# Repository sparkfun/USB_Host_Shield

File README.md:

SparkFun USB Host Shield
========================

[*SparkFun USB Host Shield (DEV-09947)*](https://www.sparkfun.com/products/9947)

The SparkFun USB Host Shield contains all of the digital logic and analog circuitry necessary to implement a full-speed USB peripheral/host controller with your Arduino. 

Repository Contents
-------------------
* **/Hardware** - All Eagle design files (.brd, .sch)

License Information
-------------------
The hardware is released under [Creative Commons ShareAlike 4.0 International](https://creativecommons.org/licenses/by-sa/4.0/).

Distributed as-is; no warranty is given.

_Check out the original USB Host Shield site from Circuits@Home [here](https://chome.nerpa.tech/arduino_usb_host_shield_projects/)._

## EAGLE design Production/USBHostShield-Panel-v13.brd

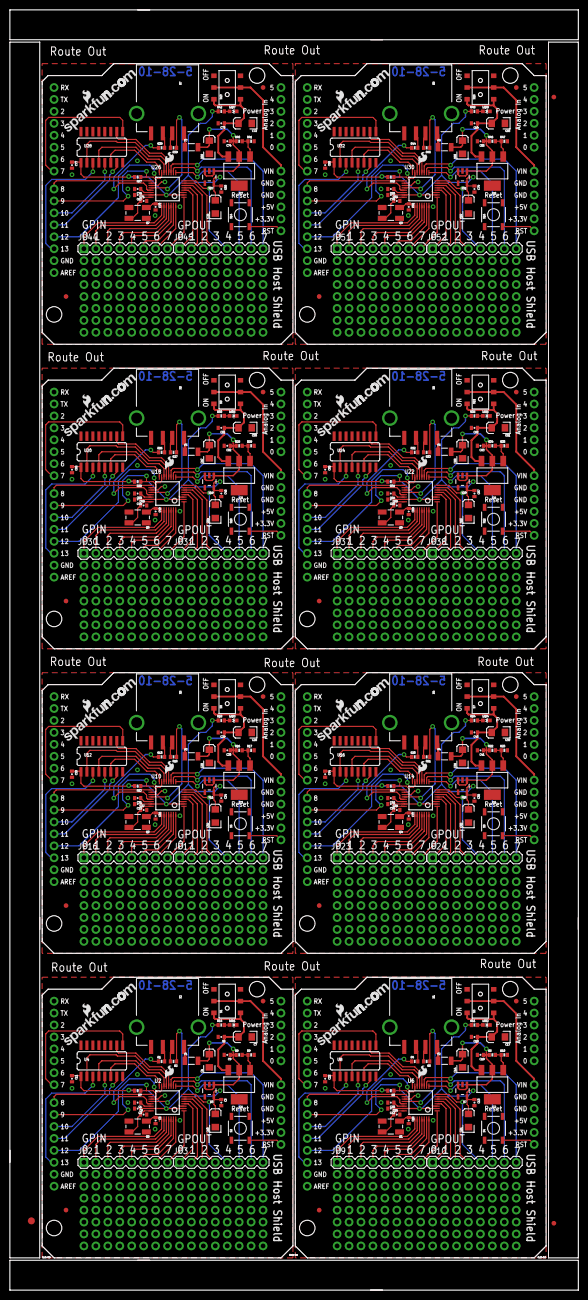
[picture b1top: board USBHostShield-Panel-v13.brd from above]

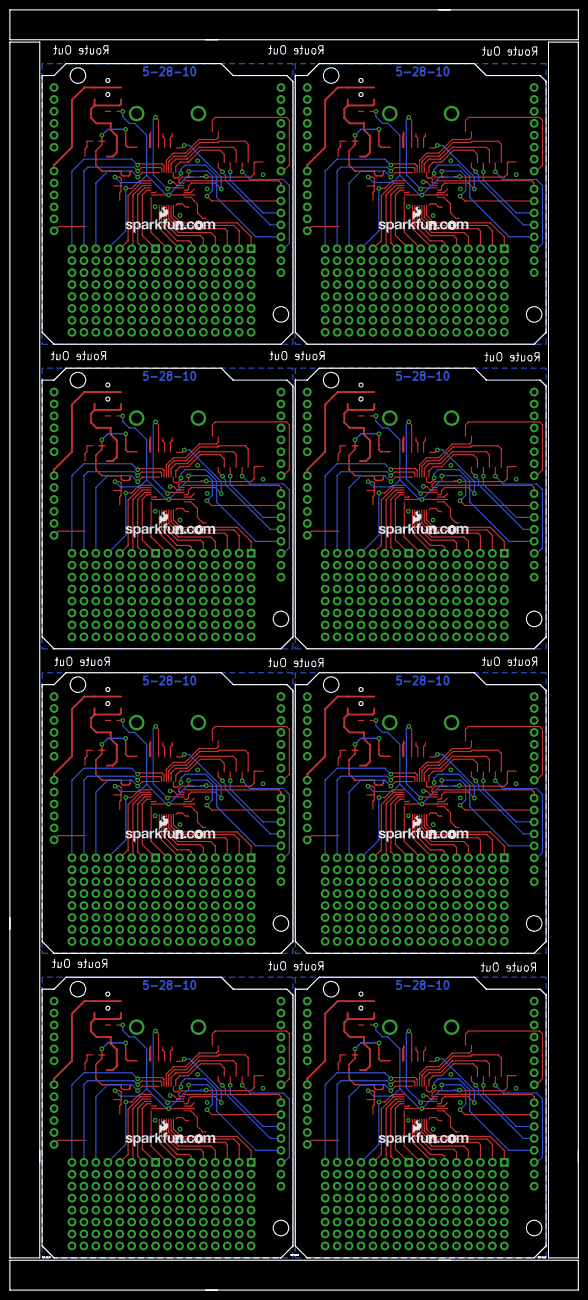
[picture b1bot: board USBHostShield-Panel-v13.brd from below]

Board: 2 copper layers, 120.9 x 272.2 mm, 283 parts (8 on the bottom side), 344 nets.

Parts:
C1, C2, C3, C8, C9, C11, C12, C13, C18, C19, C20, C22, C23, C24, C29, C30, C31, C33, C34, C35, C40, C41, C42, C44, C45, C46, C51, C52, C53, C55, C56, C57, C62, C63, C64, C66, C67, C68, C73, C74, C75, C77, C78, C79, C84, C85, C86, C88: 0.1uF; 0402-CAP
C4, C7, C10, C14, C17, C21, C25, C28, C32, C36, C39, C43, C47, C50, C54, C58, C61, C65, C69, C72, C76, C80, C83, C87: 10uF; EIA3216
C5, C6, C15, C16, C26, C27, C37, C38, C48, C49, C59, C60, C70, C71, C81, C82: 18pF; 0402-CAP
E$1: FIDUCIAL-1.5X3
E$2, E$5: FIDUCIAL-1X2
F1, F2, F3, F4, F5, F6, F7, F8: PTCSMD; PTC-1206
IC1, IC2, IC3, IC4, IC5, IC6, IC7, IC8: lm1117; SOT223
JP1, JP5, JP8, JP11, JP15, JP18, JP22, JP25, JP29, JP32, JP36, JP39, JP43, JP46, JP50, JP53: LOGO-SFENEW; SFE-NEW-WEBLOGO
JP2, JP9, JP16, JP23, JP30, JP37, JP44, JP51: GPIN; 1X08
JP3, JP10, JP17, JP24, JP31, JP38, JP45, JP52: GPOUT; 1X08
JP4, JP12, JP19, JP26, JP33, JP40, JP47, JP54: LOGO-SFESK; SFE-LOGO-FLAME
JP6, JP7, JP13, JP14, JP20, JP21, JP27, JP28, JP34, JP35, JP41, JP42, JP48, JP49, JP55, JP56: FIDUCIAL1X2; FIDUCIAL-1X2
LED1, LED2, LED3, LED4, LED5, LED6, LED7, LED8: red; LED-0603
Q1, Q2, Q3, Q4, Q5, Q6, Q7, Q8: 12MHz; CRYSTAL-SMD-5X3
R1, R2, R4, R5, R13, R15, R20, R21, R26, R27, R32, R33, R38, R39, R44, R45: 33; 0402-RES
R3, R7, R12, R19, R25, R31, R37, R43: 2.2K; 0402-RES
R6, R8, R16, R22, R28, R34, R40, R46: 240; 0402-RES
R9, R10, R17, R23, R29, R35, R41, R47: 715; 0402-RES
R11, R14, R18, R24, R30, R36, R42, R48: 330; 0402-RES
S1, S3, S5, S7, S9, S11, S13, S15: SWITCH-DPDTSMD; AYZ0202
S2, S4, S6, S8, S10, S12, S14, S16: SWITCH-SMD; TACTILE_SWITCH_SMD
U1, U5, U9, U13, U17, U21, U25, U29: ARDUINO_SHIELD; DUEMILANOVE_SHIELD
U2, U6, U10, U14, U18, U22, U26, U30: MAX3421E; TQFP32-5MM
U3, U7, U11, U15, U19, U23, U27, U31: 3.3V_REG; SOT23-5
U4, U8, U12, U16, U20, U24, U28, U32: HEX_CONVERTER; SO016
X1, X2, X3, X4, X5, X6, X7, X8: USB_; USB-A-S-SILK-FEMALE

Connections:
3.3V: C2.1, C3.1, C10.A, C11.1, R7.2, R14.1, U2.2, U2.23, U3.5, U4.1
3.3V1: C12.1, C13.1, C21.A, C22.1, R3.2, R11.1, U6.2, U6.23, U7.5, U8.1
3.3V2: C23.1, C24.1, C32.A, C33.1, R12.2, R18.1, U10.2, U10.23, U11.5, U12.1
3.3V3: C34.1, C35.1, C43.A, C44.1, R19.2, R24.1, U14.2, U14.23, U15.5, U16.1
3.3V4: C45.1, C46.1, C54.A, C55.1, R25.2, R30.1, U18.2, U18.23, U19.5, U20.1
3.3V5: C56.1, C57.1, C65.A, C66.1, R31.2, R36.1, U22.2, U22.23, U23.5, U24.1
3.3V6: C67.1, C68.1, C76.A, C77.1, R37.2, R42.1, U26.2, U26.23, U27.5, U28.1
3.3V7: C78.1, C79.1, C87.A, C88.1, R43.2, R48.1, U30.2, U30.23, U31.5, U32.1
5V: C4.A, C9.1, F1.2, IC1.2, R8.1, U3.1, U3.3
5V1: C14.A, C19.1, F2.2, IC2.2, R6.1, U7.1, U7.3
5V2: C25.A, C30.1, F3.2, IC3.2, R16.1, U11.1, U11.3
5V3: C36.A, C41.1, F4.2, IC4.2, R22.1, U15.1, U15.3
5V4: C47.A, C52.1, F5.2, IC5.2, R28.1, U19.1, U19.3
5V5: C58.A, C63.1, F6.2, IC6.2, R34.1, U23.1, U23.3
5V6: C69.A, C74.1, F7.2, IC7.2, R40.1, U27.1, U27.3
5V7: C80.A, C85.1, F8.2, IC8.2, R46.1, U31.1, U31.3
GND: C1.2, C2.2, C3.2, C4.C, C5.2, C6.2, C7.C, C8.2, C9.2, C10.C, C11.2, LED1.C, R9.2, S2.1, U1.GND@0, U1.GND@1, U1.GND@2, U2.3, U2.19, U3.2, U4.8, X2.GND
GND1: C12.2, C13.2, C14.C, C15.2, C16.2, C17.C, C18.2, C19.2, C20.2, C21.C, C22.2, LED2.C, R10.2, S4.1, U5.GND@0, U5.GND@1, U5.GND@2, U6.3, U6.19, U7.2, U8.8, X1.GND
GND2: C23.2, C24.2, C25.C, C26.2, C27.2, C28.C, C29.2, C30.2, C31.2, C32.C, C33.2, LED3.C, R17.2, S6.1, U9.GND@0, U9.GND@1, U9.GND@2, U10.3, U10.19, U11.2, U12.8, X3.GND
GND3: C34.2, C35.2, C36.C, C37.2, C38.2, C39.C, C40.2, C41.2, C42.2, C43.C, C44.2, LED4.C, R23.2, S8.1, U13.GND@0, U13.GND@1, U13.GND@2, U14.3, U14.19, U15.2, U16.8, X4.GND
GND4: C45.2, C46.2, C47.C, C48.2, C49.2, C50.C, C51.2, C52.2, C53.2, C54.C, C55.2, LED5.C, R29.2, S10.1, U17.GND@0, U17.GND@1, U17.GND@2, U18.3, U18.19, U19.2, U20.8, X5.GND
GND5: C56.2, C57.2, C58.C, C59.2, C60.2, C61.C, C62.2, C63.2, C64.2, C65.C, C66.2, LED6.C, R35.2, S12.1, U21.GND@0, U21.GND@1, U21.GND@2, U22.3, U22.19, U23.2, U24.8, X6.GND
GND6: C67.2, C68.2, C69.C, C70.2, C71.2, C72.C, C73.2, C74.2, C75.2, C76.C, C77.2, LED7.C, R41.2, S14.1, U25.GND@0, U25.GND@1, U25.GND@2, U26.3, U26.19, U27.2, U28.8, X7.GND
GND7: C78.2, C79.2, C80.C, C81.2, C82.2, C83.C, C84.2, C85.2, C86.2, C87.C, C88.2, LED8.C, R47.2, S16.1, U29.GND@0, U29.GND@1, U29.GND@2, U30.3, U30.19, U31.2, U32.8, X8.GND
GPX: U1.D8, U2.17
GPX1: U5.D8, U6.17
GPX2: U9.D8, U10.17
GPX3: U13.D8, U14.17
GPX4: U17.D8, U18.17
GPX5: U21.D8, U22.17
GPX6: U25.D8, U26.17
GPX7: U29.D8, U30.17
INT: R7.1, U1.D9, U2.18
INT1: R3.1, U5.D9, U6.18
INT2: R12.1, U9.D9, U10.18
INT3: R19.1, U13.D9, U14.18
INT4: R25.1, U17.D9, U18.18
INT5: R31.1, U21.D9, U22.18
INT6: R37.1, U25.D9, U26.18
INT7: R43.1, U29.D9, U30.18
MISO: U1.D12, U2.15
MISO1: U5.D12, U6.15
MISO2: U9.D12, U10.15
MISO3: U13.D12, U14.15
MISO4: U17.D12, U18.15
MISO5: U21.D12, U22.15
MISO6: U25.D12, U26.15
MISO7: U29.D12, U30.15
MOSI: U1.D11, U4.7
MOSI1: U5.D11, U8.7
MOSI2: U9.D11, U12.7
MOSI3: U13.D11, U16.7
MOSI4: U17.D11, U20.7
MOSI5: U21.D11, U24.7
MOSI6: U25.D11, U28.7
MOSI7: U29.D11, U32.7
MOSI-IN: U2.16, U4.6
MOSI-IN1: U6.16, U8.6
MOSI-IN2: U10.16, U12.6
MOSI-IN3: U14.16, U16.6
MOSI-IN4: U18.16, U20.6
MOSI-IN5: U22.16, U24.6
MOSI-IN6: U26.16, U28.6
MOSI-IN7: U30.16, U32.6
unnamed: JP2.8, U2.1
unnamed: R2.1, U2.20
unnamed: R1.1, U2.21
unnamed: JP3.1, U2.4
unnamed: R1.2, X2.D+
unnamed: JP3.2, U2.5
unnamed: JP3.3, U2.6
unnamed: R2.2, X2.D-
unnamed: C5.1, Q2.1, U2.25
unnamed: C6.1, Q2.3, U2.24
unnamed: IC1.1, R8.2, R9.1
unnamed: S2.3, U1.RES
unnamed: JP3.4, U2.7
unnamed: JP3.5, U2.8
unnamed: JP3.6, U2.9
unnamed: JP3.7, U2.10
unnamed: JP3.8, U2.11
unnamed: JP2.7, U2.32
unnamed: JP2.6, U2.31
unnamed: JP2.5, U2.30
unnamed: JP2.4, U2.29
unnamed: JP2.3, U2.28
unnamed: JP2.2, U2.27
unnamed: JP2.1, U2.26
unnamed: LED1.A, R14.2
unnamed: F1.1, X2.VBUS
unnamed: R4.2, X1.D+
unnamed: R5.2, X1.D-
unnamed: R5.1, U6.20
unnamed: R4.1, U6.21
unnamed: C15.1, Q1.1, U6.25
unnamed: C16.1, Q1.3, U6.24
unnamed: IC2.1, R6.2, R10.1
unnamed: JP9.8, U6.1
unnamed: JP10.1, U6.4
unnamed: JP10.2, U6.5
unnamed: JP10.3, U6.6
unnamed: JP10.4, U6.7
unnamed: JP10.5, U6.8
unnamed: JP10.6, U6.9
unnamed: JP10.7, U6.10
unnamed: JP10.8, U6.11
unnamed: JP9.7, U6.32
unnamed: JP9.6, U6.31
unnamed: JP9.5, U6.30
unnamed: JP9.4, U6.29
unnamed: JP9.3, U6.28
unnamed: JP9.2, U6.27
unnamed: JP9.1, U6.26
unnamed: S4.3, U5.RES
unnamed: LED2.A, R11.2
unnamed: F2.1, X1.VBUS
unnamed: R13.2, X3.D+
unnamed: R15.2, X3.D-
unnamed: R15.1, U10.20
unnamed: R13.1, U10.21
unnamed: C26.1, Q3.1, U10.25
unnamed: C27.1, Q3.3, U10.24
unnamed: IC3.1, R16.2, R17.1
unnamed: JP16.8, U10.1
unnamed: JP17.1, U10.4
unnamed: JP17.2, U10.5
unnamed: JP17.3, U10.6
unnamed: JP17.4, U10.7
unnamed: JP17.5, U10.8
unnamed: JP17.6, U10.9
unnamed: JP17.7, U10.10
unnamed: JP17.8, U10.11
unnamed: JP16.7, U10.32
unnamed: JP16.6, U10.31
unnamed: JP16.5, U10.30
unnamed: JP16.4, U10.29
unnamed: JP16.3, U10.28
unnamed: JP16.2, U10.27
unnamed: JP16.1, U10.26
unnamed: S6.3, U9.RES
unnamed: LED3.A, R18.2
unnamed: F3.1, X3.VBUS
unnamed: R20.2, X4.D+
unnamed: R21.2, X4.D-
unnamed: R21.1, U14.20
unnamed: R20.1, U14.21
unnamed: C37.1, Q4.1, U14.25
unnamed: C38.1, Q4.3, U14.24
unnamed: IC4.1, R22.2, R23.1
unnamed: JP23.8, U14.1
unnamed: JP24.1, U14.4
unnamed: JP24.2, U14.5
unnamed: JP24.3, U14.6
unnamed: JP24.4, U14.7
unnamed: JP24.5, U14.8
unnamed: JP24.6, U14.9
unnamed: JP24.7, U14.10
unnamed: JP24.8, U14.11
unnamed: JP23.7, U14.32
unnamed: JP23.6, U14.31
unnamed: JP23.5, U14.30
unnamed: JP23.4, U14.29
unnamed: JP23.3, U14.28
unnamed: JP23.2, U14.27
unnamed: JP23.1, U14.26
unnamed: S8.3, U13.RES
unnamed: LED4.A, R24.2
unnamed: F4.1, X4.VBUS
unnamed: R26.2, X5.D+
unnamed: R27.2, X5.D-
unnamed: R27.1, U18.20
unnamed: R26.1, U18.21
unnamed: C48.1, Q5.1, U18.25
unnamed: C49.1, Q5.3, U18.24
unnamed: IC5.1, R28.2, R29.1
unnamed: JP30.8, U18.1
unnamed: JP31.1, U18.4
unnamed: JP31.2, U18.5
unnamed: JP31.3, U18.6
unnamed: JP31.4, U18.7
unnamed: JP31.5, U18.8
unnamed: JP31.6, U18.9
unnamed: JP31.7, U18.10
unnamed: JP31.8, U18.11
unnamed: JP30.7, U18.32
unnamed: JP30.6, U18.31
unnamed: JP30.5, U18.30
unnamed: JP30.4, U18.29
unnamed: JP30.3, U18.28
unnamed: JP30.2, U18.27
unnamed: JP30.1, U18.26
unnamed: S10.3, U17.RES
unnamed: LED5.A, R30.2
unnamed: F5.1, X5.VBUS
unnamed: R32.2, X6.D+
unnamed: R33.2, X6.D-
unnamed: R33.1, U22.20
unnamed: R32.1, U22.21
unnamed: C59.1, Q6.1, U22.25
unnamed: C60.1, Q6.3, U22.24
unnamed: IC6.1, R34.2, R35.1
unnamed: JP37.8, U22.1
unnamed: JP38.1, U22.4
unnamed: JP38.2, U22.5
unnamed: JP38.3, U22.6
unnamed: JP38.4, U22.7
unnamed: JP38.5, U22.8
unnamed: JP38.6, U22.9
unnamed: JP38.7, U22.10
unnamed: JP38.8, U22.11
unnamed: JP37.7, U22.32
unnamed: JP37.6, U22.31
unnamed: JP37.5, U22.30
unnamed: JP37.4, U22.29
unnamed: JP37.3, U22.28
unnamed: JP37.2, U22.27
unnamed: JP37.1, U22.26
unnamed: S12.3, U21.RES
unnamed: LED6.A, R36.2
unnamed: F6.1, X6.VBUS
unnamed: R38.2, X7.D+
unnamed: R39.2, X7.D-
unnamed: R39.1, U26.20
unnamed: R38.1, U26.21
unnamed: C70.1, Q7.1, U26.25
unnamed: C71.1, Q7.3, U26.24
unnamed: IC7.1, R40.2, R41.1
unnamed: JP44.8, U26.1
unnamed: JP45.1, U26.4
unnamed: JP45.2, U26.5
unnamed: JP45.3, U26.6
unnamed: JP45.4, U26.7
unnamed: JP45.5, U26.8
unnamed: JP45.6, U26.9
unnamed: JP45.7, U26.10
unnamed: JP45.8, U26.11
unnamed: JP44.7, U26.32
unnamed: JP44.6, U26.31
unnamed: JP44.5, U26.30
unnamed: JP44.4, U26.29
unnamed: JP44.3, U26.28
unnamed: JP44.2, U26.27
unnamed: JP44.1, U26.26
unnamed: S14.3, U25.RES
unnamed: LED7.A, R42.2
unnamed: F7.1, X7.VBUS
unnamed: R44.2, X8.D+
unnamed: R45.2, X8.D-
unnamed: R45.1, U30.20
unnamed: R44.1, U30.21
unnamed: C81.1, Q8.1, U30.25
unnamed: C82.1, Q8.3, U30.24
unnamed: IC8.1, R46.2, R47.1
unnamed: JP51.8, U30.1
unnamed: JP52.1, U30.4
unnamed: JP52.2, U30.5
unnamed: JP52.3, U30.6
unnamed: JP52.4, U30.7
unnamed: JP52.5, U30.8
unnamed: JP52.6, U30.9
unnamed: JP52.7, U30.10
unnamed: JP52.8, U30.11
unnamed: JP51.7, U30.32
unnamed: JP51.6, U30.31
unnamed: JP51.5, U30.30
unnamed: JP51.4, U30.29
unnamed: JP51.3, U30.28
unnamed: JP51.2, U30.27
unnamed: JP51.1, U30.26
unnamed: S16.3, U29.RES
unnamed: LED8.A, R48.2
unnamed: F8.1, X8.VBUS
RESET: U1.D7, U4.9
RESET1: U5.D7, U8.9
RESET2: U9.D7, U12.9
RESET3: U13.D7, U16.9
RESET4: U17.D7, U20.9
RESET5: U21.D7, U24.9
RESET6: U25.D7, U28.9
RESET7: U29.D7, U32.9
RESET-IN: U2.12, U4.10
RESET-IN1: U6.12, U8.10
RESET-IN2: U10.12, U12.10
RESET-IN3: U14.12, U16.10
RESET-IN4: U18.12, U20.10
RESET-IN5: U22.12, U24.10
RESET-IN6: U26.12, U28.10
RESET-IN7: U30.12, U32.10
SCK: U1.D13, U4.3
SCK1: U5.D13, U8.3
SCK2: U9.D13, U12.3
SCK3: U13.D13, U16.3
SCK4: U17.D13, U20.3
SCK5: U21.D13, U24.3
SCK6: U25.D13, U28.3
SCK7: U29.D13, U32.3
SCK-IN: U2.13, U4.2
SCK-IN1: U6.13, U8.2
SCK-IN2: U10.13, U12.2
SCK-IN3: U14.13, U16.2
SCK-IN4: U18.13, U20.2
SCK-IN5: U22.13, U24.2
SCK-IN6: U26.13, U28.2
SCK-IN7: U30.13, U32.2
SS: U1.D10, U4.5
SS1: U5.D10, U8.5
SS2: U9.D10, U12.5
SS3: U13.D10, U16.5
SS4: U17.D10, U20.5
SS5: U21.D10, U24.5
SS6: U25.D10, U28.5
SS7: U29.D10, U32.5
SS-IN: U2.14, U4.4
SS-IN1: U6.14, U8.4
SS-IN2: U10.14, U12.4
SS-IN3: U14.14, U16.4
SS-IN4: U18.14, U20.4
SS-IN5: U22.14, U24.4
SS-IN6: U26.14, U28.4
SS-IN7: U30.14, U32.4
VBCOMP: C1.1, U2.22
VBCOMP1: C20.1, U6.22
VBCOMP2: C31.1, U10.22
VBCOMP3: C42.1, U14.22
VBCOMP4: C53.1, U18.22
VBCOMP5: C64.1, U22.22
VBCOMP6: C75.1, U26.22
VBCOMP7: C86.1, U30.22
VBUS: C7.A, C8.1, IC1.3, S1.1, S1.4
VBUS1: C17.A, C18.1, IC2.3, S3.1, S3.4
VBUS2: C28.A, C29.1, IC3.3, S5.1, S5.4
VBUS3: C39.A, C40.1, IC4.3, S7.1, S7.4
VBUS4: C50.A, C51.1, IC5.3, S9.1, S9.4
VBUS5: C61.A, C62.1, IC6.3, S11.1, S11.4
VBUS6: C72.A, C73.1, IC7.3, S13.1, S13.4
VBUS7: C83.A, C84.1, IC8.3, S15.1, S15.4
VIN: S1.2, S1.5, U1.VIN
VIN1: S3.2, S3.5, U5.VIN
VIN2: S5.2, S5.5, U9.VIN
VIN3: S7.2, S7.5, U13.VIN
VIN4: S9.2, S9.5, U17.VIN
VIN5: S11.2, S11.5, U21.VIN
VIN6: S13.2, S13.5, U25.VIN
VIN7: S15.2, S15.5, U29.VIN

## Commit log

2015-03-10 Adding hardware files, updating README
2015-03-10 Adding link to original project by Oleg
2015-10-22 created panel v13
2021-02-24 Update README.md
    The domain changed a while ago (sometime after April 2019). Looking at the GitHub repo for the USB Host Shield Arduino Library, it points to a different website for the board. Updating the link to av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

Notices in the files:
parts and their libraries:
SparkFun-Aesthetics: Licensing: CC v3.0 Share-Alike You are welcome to use this library for commercial purposes.
SparkFun-Retired: Licensing:Creative Commons ShareAlike 4.0 International - https://creativecommons.org/licenses/by-sa/4.0
